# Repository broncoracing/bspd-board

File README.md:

# BSPD 
Bronco Racing Brake System Plausibility Device for BREV25

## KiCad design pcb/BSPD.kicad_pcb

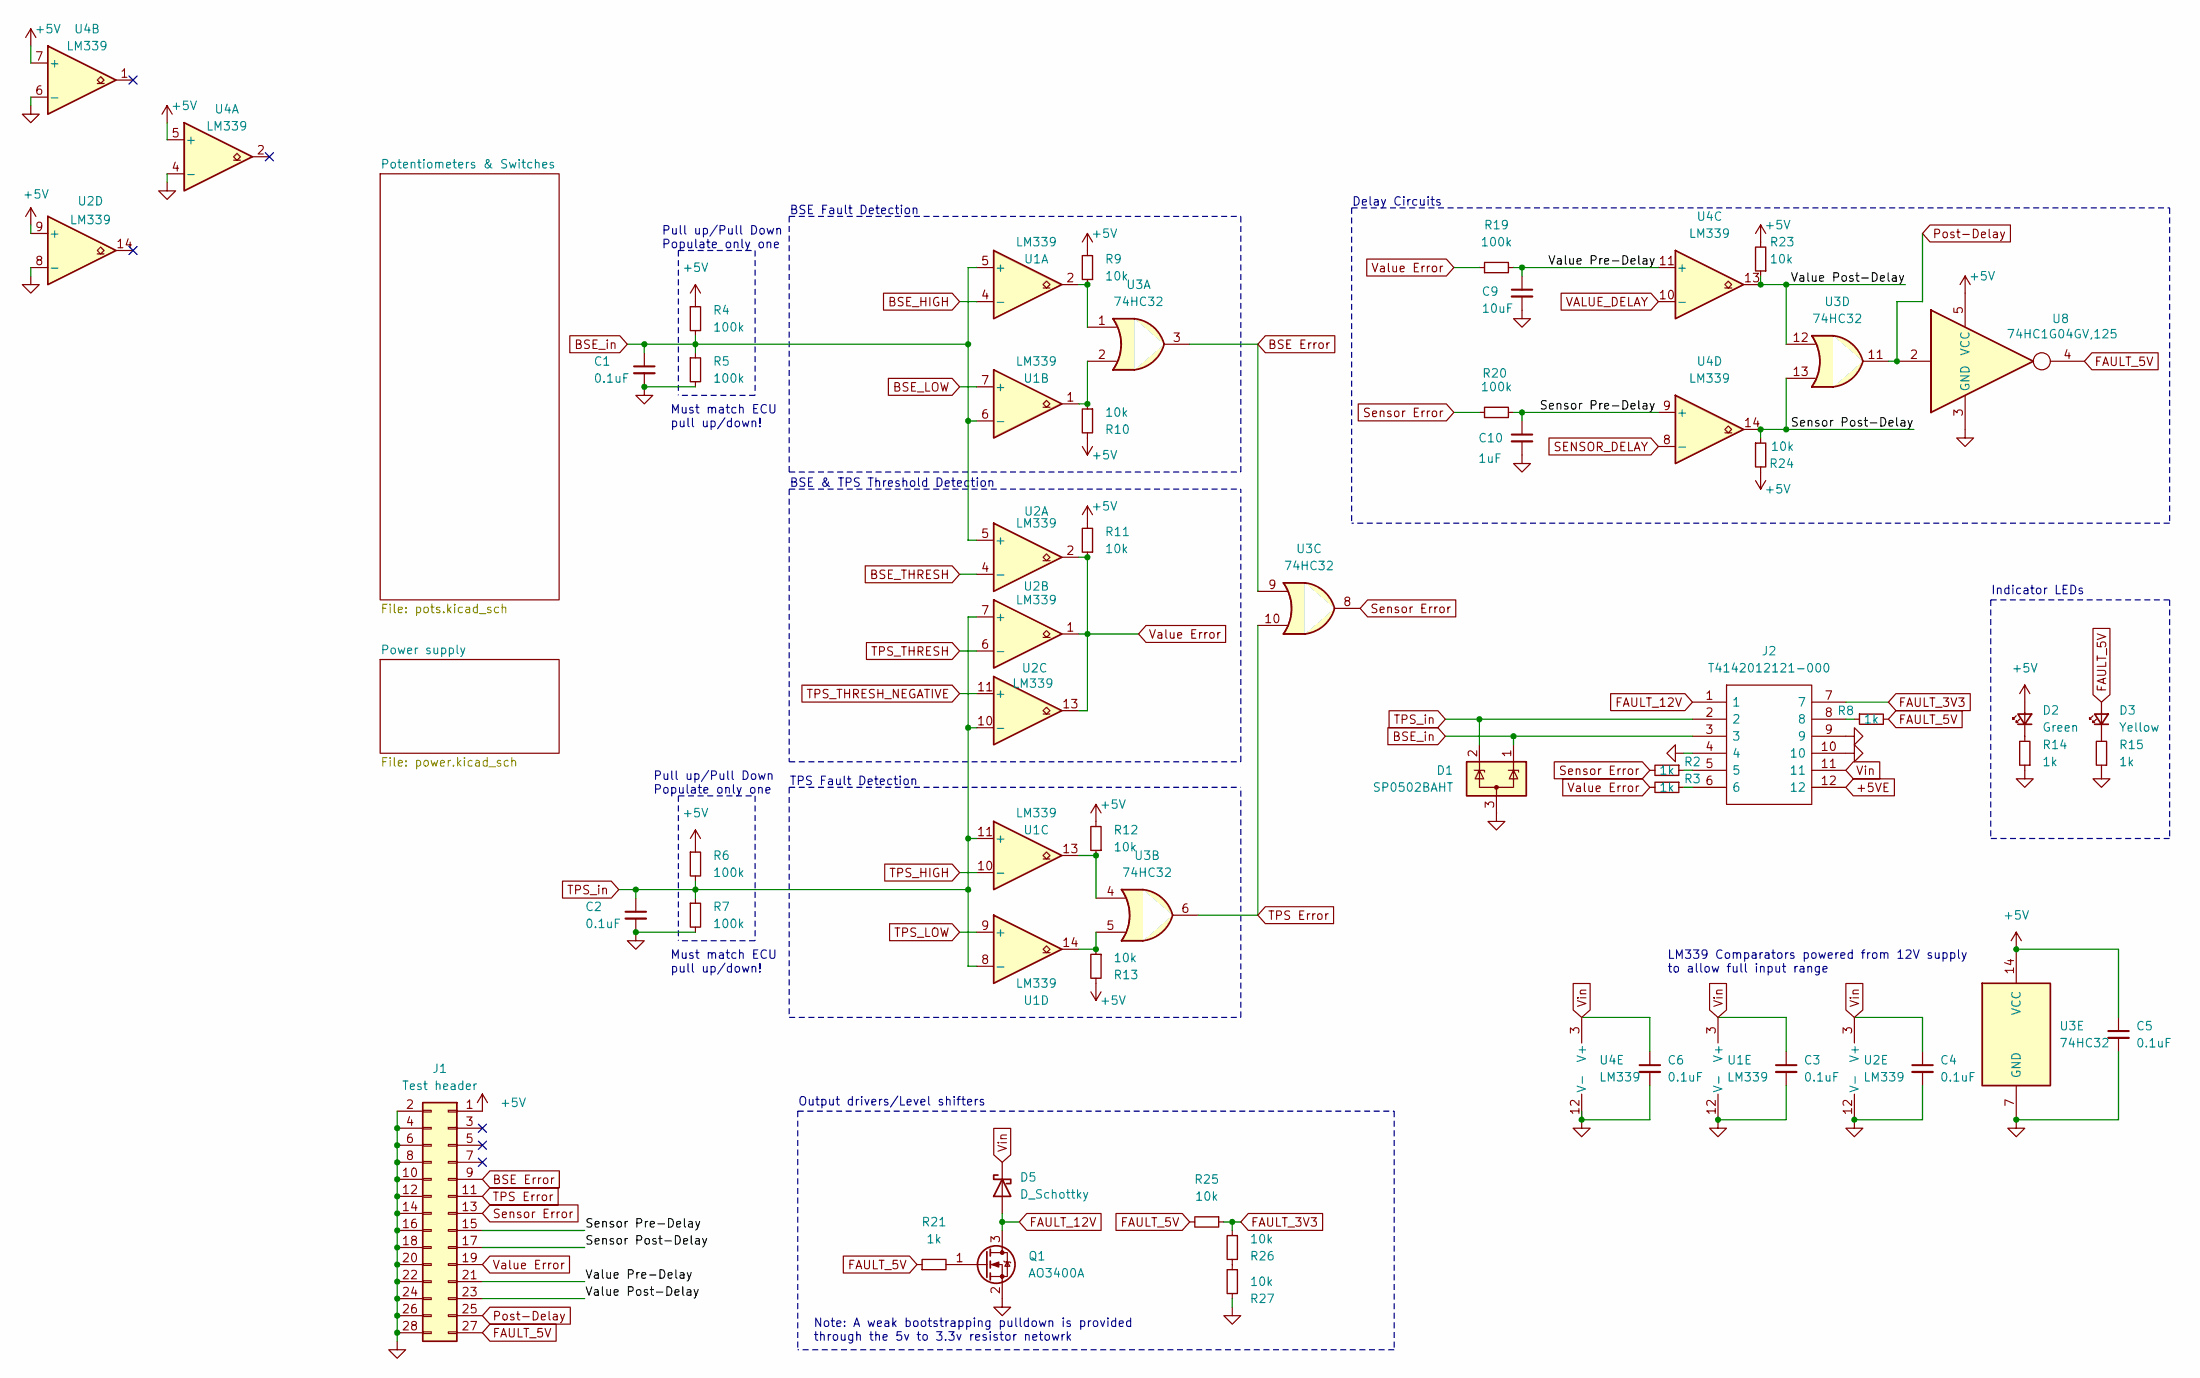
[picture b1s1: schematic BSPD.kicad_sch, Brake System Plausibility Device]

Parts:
C1, C2, C3, C4, C5, C6: 0.1uF; C_0402_1005Metric; LCSC C307331
C9: 10uF; C_0805_2012Metric; LCSC C440198
C10: 1uF; C_0402_1005Metric; LCSC C52923
D1: SP0502BAHT; SOT-23; LCSC C32677
D2: Green; LED_0603_1608Metric; LCSC C72043
D3: Yellow; LED_0603_1608Metric; LCSC C72038
D5: D_Schottky; D_SOD-323; LCSC C191023
J1: Test header; PinHeader_2x14_P2.54mm_Vertical
J2: T4142012121-000; T4140012121000; Mouser Part Number 571-T4142012121-000
Q1: AO3400A; SOT-23; LCSC C20917
R2, R3, R8, R14, R15, R21: 1k; R_0402_1005Metric; LCSC C11702
R4, R5, R6, R7, R19, R20: 100k; R_0402_1005Metric; LCSC C25741
R9, R10, R11, R12, R13, R23, R24, R25, R26, R27: 10k; R_0402_1005Metric; LCSC C25744
U1, U2: LM339; SOIC-14_3.9x8.7mm_P1.27mm; LCSC C63821
U3: 74HC32; SOIC-14_3.9x8.7mm_P1.27mm; LCSC C6838
U4: LM339; SOIC-14_3.9x8.7mm_P1.27mm
U8: 74HC1G04GV,125; SOT-553

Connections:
+5V: C5.1, D2.2 (A), J1.1, R4.1, R6.1, R9.2, R10.2, R11.2, R12.2, R13.2, R23.2, R24.2, U2.9 (+), U3.14 (VCC), U4.5 (+), U4.7 (+), U8.5 (VCC); also elsewhere on the board
+5VE: J2.12; also elsewhere on the board
/Sensor Post-Delay: J1.17, R24.1, U3.13, U4.14
/Sensor Pre-Delay: C10.1, J1.15, R20.2, U4.9 (+)
/Value Post-Delay: J1.23, R23.1, U3.12, U4.13
/Value Pre-Delay: C9.1, J1.21, R19.2, U4.11 (+)
BSE Error: J1.9, U3.3, U3.9
BSE_HIGH: U1.4 (-); also elsewhere on the board
BSE_LOW: U1.7 (+); also elsewhere on the board
BSE_THRESH: U2.4 (-); also elsewhere on the board
BSE_in: C1.1, D1.1 (K), J2.3, R4.2, R5.1, U1.5 (+), U1.6 (-), U2.5 (+)
FAULT_3V3: J2.7, R25.1, R26.1
FAULT_5V: D3.2 (A), J1.27, R8.2, R21.1, R25.2, U8.4
FAULT_12V: D5.2 (A), J2.1, Q1.3 (D)
GND: C1.2, C2.2, C3.2, C4.2, C5.2, C6.2, C9.2, C10.2, D1.3 (A), J1.2, J1.4, J1.6, J1.8, J1.10, J1.12, J1.14, J1.16, J1.18, J1.20, J1.22, J1.24, J1.26, J1.28, J2.4, J2.9, J2.10, Q1.2 (S), R5.2, R7.2, R14.1, R15.1, R27.2, U1.12 (V-), U2.8 (-), U2.12 (V-), U3.7 (GND), U4.4 (-), U4.6 (-), U4.12 (V-), U8.3 (GND); also elsewhere on the board
unnamed: D2.1 (K), R14.2
unnamed: D3.1 (K), R15.2
unnamed: J2.5, R2.1
unnamed: J2.6, R3.1
unnamed: J2.8, R8.1
unnamed: Q1.1 (G), R21.2
unnamed: R9.1, U1.2, U3.1
unnamed: R10.1, U1.1, U3.2
unnamed: R12.1, U1.13, U3.4
unnamed: R13.1, U1.14, U3.5
unnamed: R26.2, R27.1
Post-Delay: J1.25, U3.11, U8.2
SENSOR_DELAY: U4.8 (-); also elsewhere on the board
Sensor Error: J1.13, R2.2, R20.1, U3.8
TPS Error: J1.11, U3.6, U3.10
TPS_HIGH: U1.10 (-); also elsewhere on the board
TPS_LOW: U1.9 (+); also elsewhere on the board
TPS_THRESH: U2.6 (-); also elsewhere on the board
TPS_THRESH_NEGATIVE: U2.11 (+); also elsewhere on the board
TPS_in: C2.1, D1.2 (K), J2.2, R6.2, R7.1, U1.8 (-), U1.11 (+), U2.7 (+), U2.10 (-)
VALUE_DELAY: U4.10 (-); also elsewhere on the board
Value Error: J1.19, R3.2, R11.1, R19.1, U2.1, U2.2, U2.13
Vin: C3.1, C4.1, C6.1, D5.1 (K), J2.11, U1.3 (V+), U2.3 (V+), U4.3 (V+); also elsewhere on the board

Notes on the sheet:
Pull up/Pull Down Populate only one
Delay Circuits
TPS Fault Detection
LM339 Comparators powered from 12V supply to allow full input range
Must match ECU pull up/down!
Indicator LEDs
Output drivers/Level shifters
BSE Fault Detection
BSE & TPS Threshold Detection
Note: A weak bootstrapping pulldown is provided through the 5v to 3.3v resistor netowrk

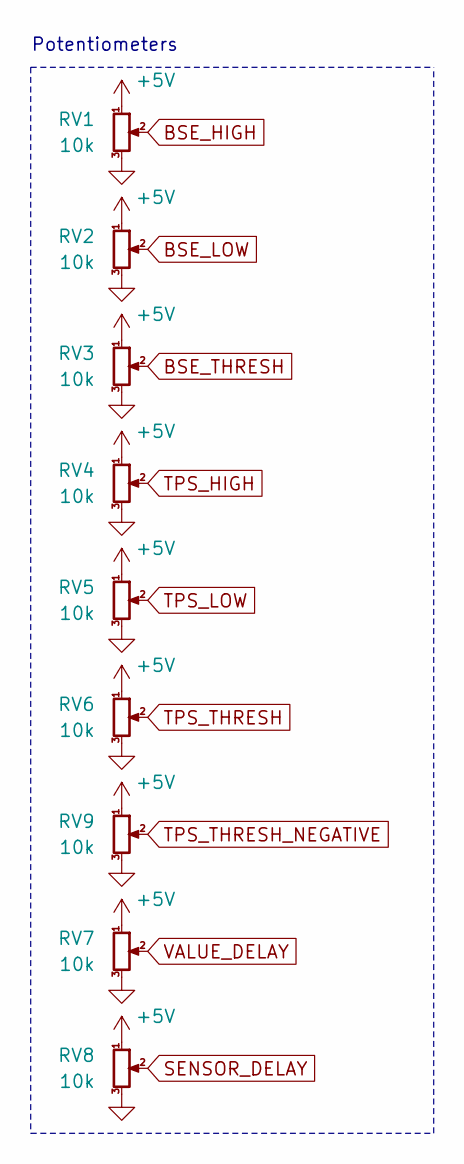
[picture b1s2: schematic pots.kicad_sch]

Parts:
RV1, RV2, RV3, RV4, RV5, RV6, RV7, RV8, RV9: 10k; Potentiometer_Bourns_TC33X_Vertical; LCSC C719176

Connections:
+5V: RV1.1, RV2.1, RV3.1, RV4.1, RV5.1, RV6.1, RV7.1, RV8.1, RV9.1; also elsewhere on the board
BSE_HIGH: RV1.2; also elsewhere on the board
BSE_LOW: RV2.2; also elsewhere on the board
BSE_THRESH: RV3.2; also elsewhere on the board
GND: RV1.3, RV2.3, RV3.3, RV4.3, RV5.3, RV6.3, RV7.3, RV8.3, RV9.3; also elsewhere on the board
SENSOR_DELAY: RV8.2; also elsewhere on the board
TPS_HIGH: RV4.2; also elsewhere on the board
TPS_LOW: RV5.2; also elsewhere on the board
TPS_THRESH: RV6.2; also elsewhere on the board
TPS_THRESH_NEGATIVE: RV9.2; also elsewhere on the board
VALUE_DELAY: RV7.2; also elsewhere on the board

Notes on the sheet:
Potentiometers

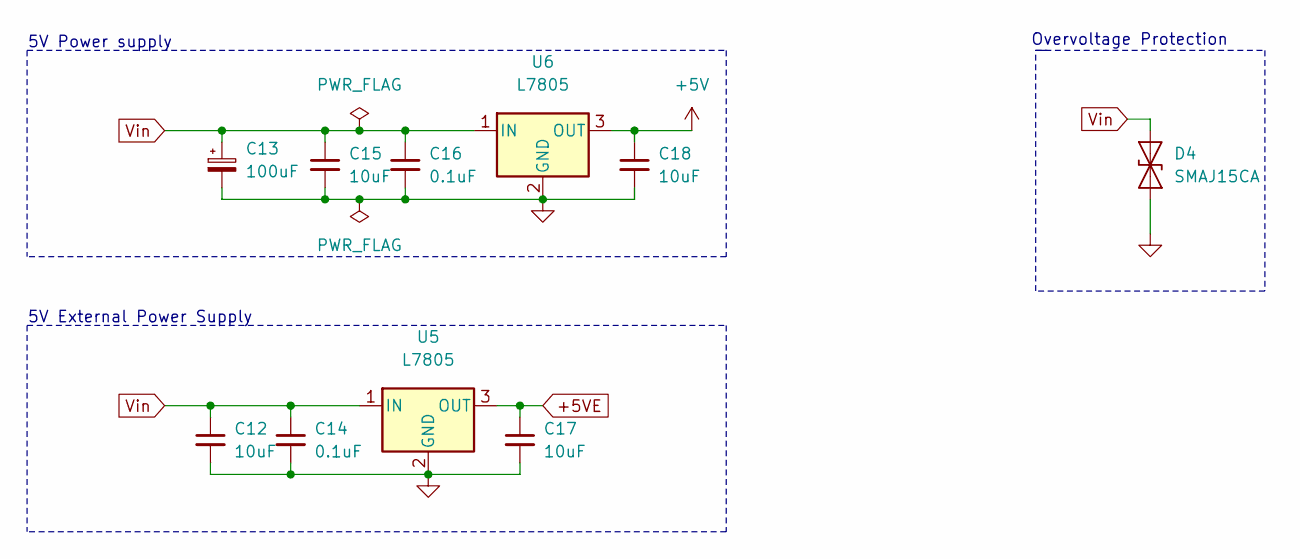
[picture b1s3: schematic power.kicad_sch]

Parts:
C12, C15, C17, C18: 10uF; C_0805_2012Metric; LCSC C440198
C13: 100uF; C_Elec_6.3x7.7; LCSC C2836437
C14, C16: 0.1uF; C_0402_1005Metric; LCSC C307331
D4: SMAJ15CA; D_SMA
U5, U6: L7805; TO-252-2; LCSC C897464

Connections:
+5V: C18.1, U6.3 (OUT); also elsewhere on the board
+5VE: C17.1, U5.3 (OUT); also elsewhere on the board
GND: C12.2, C13.2, C14.2, C15.2, C16.2, C17.2, C18.2, D4.1 (A1), U5.2 (GND), U6.2 (GND); also elsewhere on the board
Vin: C12.1, C13.1, C14.1, C15.1, C16.1, D4.2 (A2), U5.1 (IN), U6.1 (IN); also elsewhere on the board

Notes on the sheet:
Overvoltage Protection
5V External Power Supply
5V Power supply

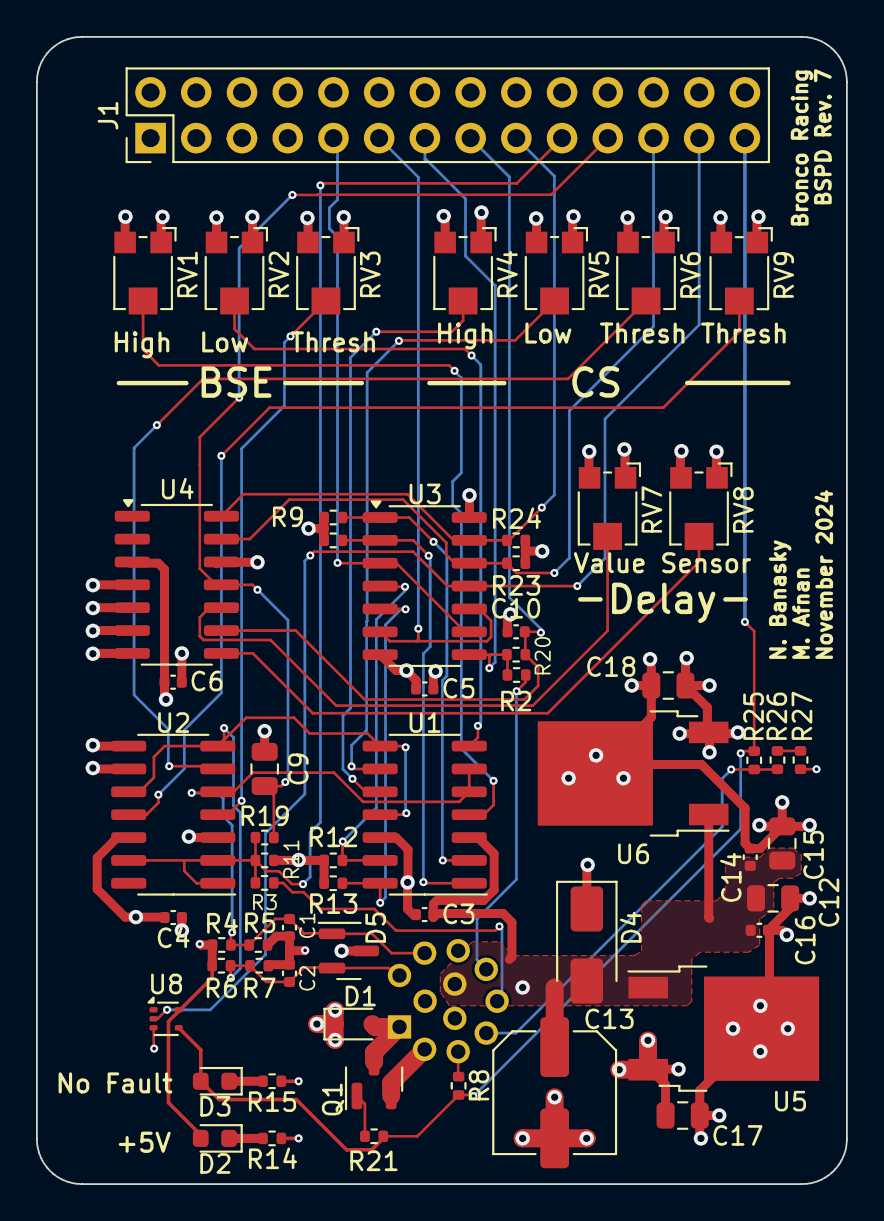
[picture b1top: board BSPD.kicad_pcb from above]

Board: 4 copper layers, 45.0 x 63.7 mm, 61 parts (1 on the bottom side), 38 nets.

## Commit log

2024-11-05 CI/CD Changes
2024-11-15 update PCB file to new kicad version
2024-11-16 Initial Schematic and PCB changes for BR2025
2024-11-16 Fixed deletion merge
2024-11-19 change pcb layout
2024-11-22 Small changes to silkscreen and fixed drc
2024-11-22 Design checklist changes
2024-11-22 Remove lck files
2024-12-02 trace routing improvements and fixed inverter mistake
